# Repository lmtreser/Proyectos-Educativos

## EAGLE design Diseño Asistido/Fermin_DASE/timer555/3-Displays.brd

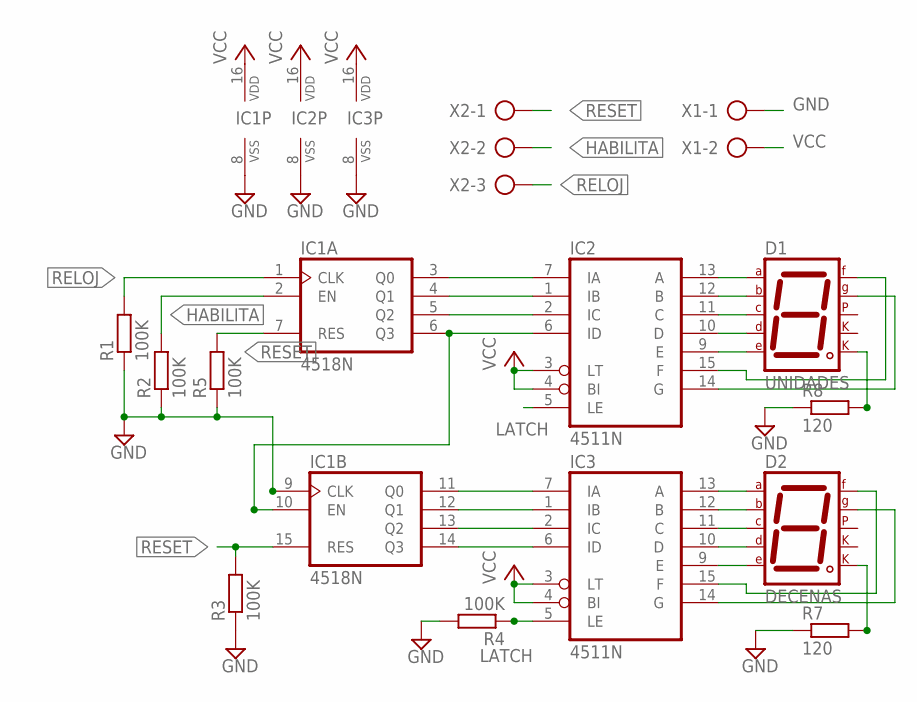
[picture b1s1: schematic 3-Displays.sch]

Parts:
D1: UNIDADES; 7SEG-13
D2: DECENAS; 7SEG-13
IC1: 4518N; DIL16
IC2, IC3: 4511N; DIL16
R1, R2, R3, R4, R5: 100K; 0207/7
R7, R8: 120; 0207/7
X1: AK500/2-H
X2: AK500/3-H

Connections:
GND: IC1.8 (VSS), IC1.9 (CLK), IC2.8 (VSS), IC3.8 (VSS), R1.1, R2.1, R3.1, R4.2, R5.1, R7.1, R8.1, X1.1
HABILITA: IC1.2 (EN), R2.2, X2.2
LATCH: IC2.5 (LE), IC3.5 (LE), R4.1
unnamed: IC1.3 (Q0), IC2.7 (IA)
unnamed: IC1.4 (Q1), IC2.1 (IB)
unnamed: IC1.5 (Q2), IC2.2 (IC)
unnamed: D1.8 (CK2), R8.2
unnamed: D2.7 (A), IC3.13 (A)
unnamed: D2.6 (B), IC3.12 (B)
unnamed: D2.4 (C), IC3.11 (C)
unnamed: D2.2 (D), IC3.10 (D)
unnamed: D2.1 (E), IC3.9 (E)
unnamed: IC1.11 (Q0), IC3.7 (IA)
unnamed: IC1.12 (Q1), IC3.1 (IB)
unnamed: IC1.14 (Q3), IC3.6 (ID)
unnamed: IC1.13 (Q2), IC3.2 (IC)
unnamed: D2.9 (F), IC3.15 (F)
unnamed: D2.10 (G), IC3.14 (G)
unnamed: D2.8 (CK2), R7.2
unnamed: D1.7 (A), IC2.13 (A)
unnamed: D1.6 (B), IC2.12 (B)
unnamed: D1.4 (C), IC2.11 (C)
unnamed: D1.2 (D), IC2.10 (D)
unnamed: D1.1 (E), IC2.9 (E)
unnamed: D1.9 (F), IC2.15 (F)
unnamed: D1.10 (G), IC2.14 (G)
unnamed: IC1.6 (Q3), IC1.10 (EN), IC2.6 (ID)
RELOJ: IC1.1 (CLK), R1.2, X2.3
RESET: IC1.7 (RES), IC1.15 (RES), R3.2, R5.2, X2.1
VCC: IC1.16 (VDD), IC2.3 (LT), IC2.4 (BI), IC2.16 (VDD), IC3.3 (LT), IC3.4 (BI), IC3.16 (VDD), X1.2

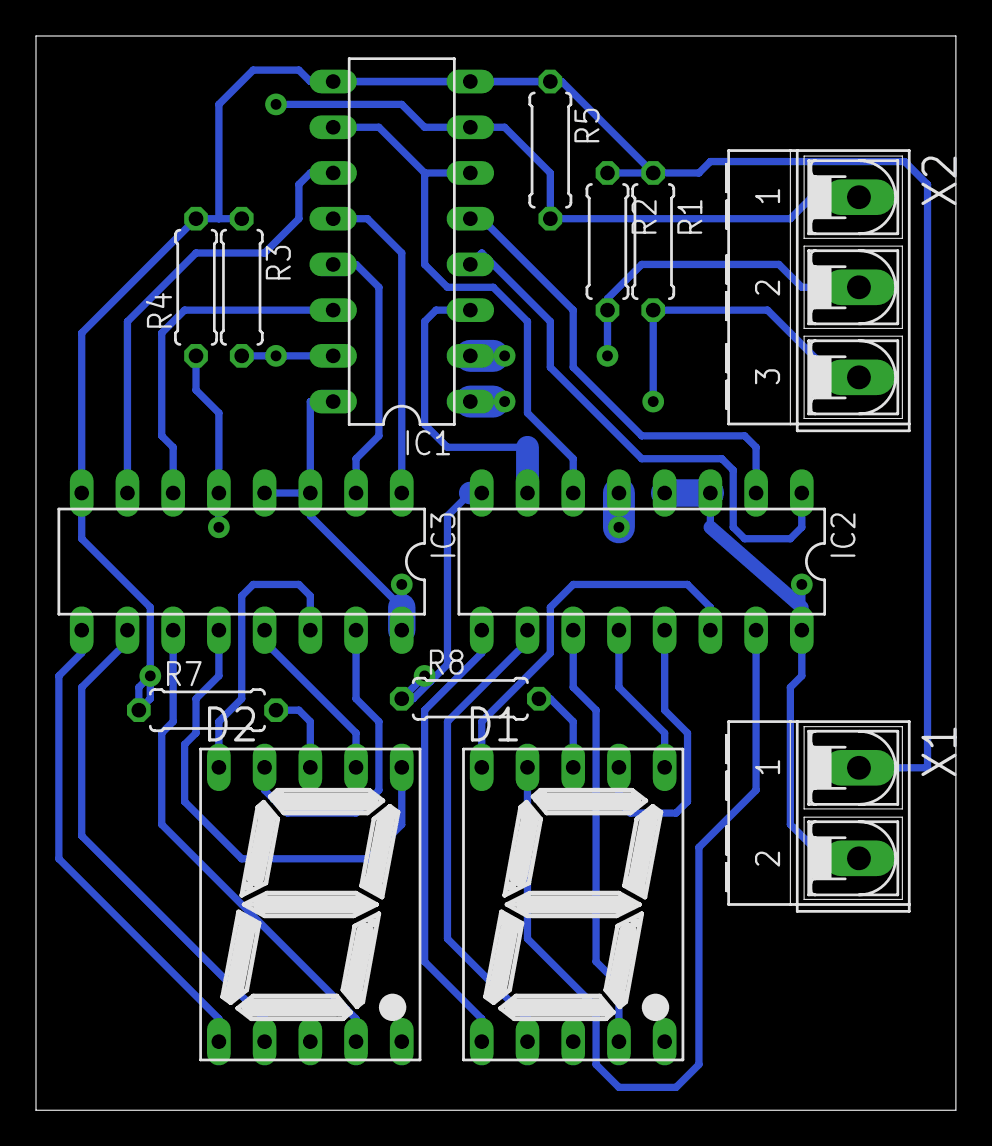
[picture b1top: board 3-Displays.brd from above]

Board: 2 copper layers, 51.1 x 59.7 mm, 14 parts (0 on the bottom side), 30 nets.

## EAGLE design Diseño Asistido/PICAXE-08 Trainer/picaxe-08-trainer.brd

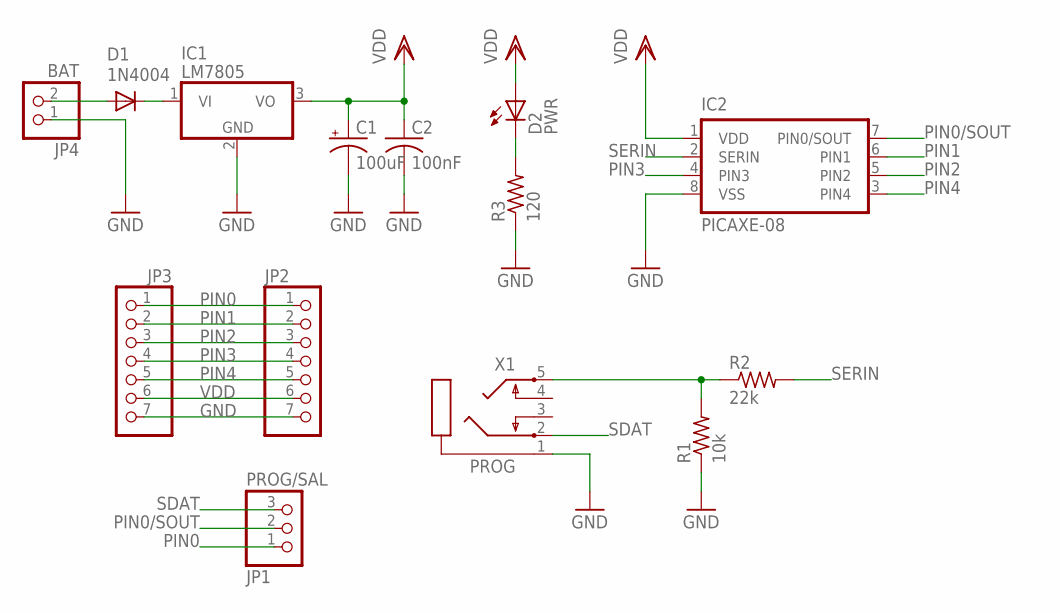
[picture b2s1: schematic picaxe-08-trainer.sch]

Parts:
C1: 100uF; E5-6
C2: 100nF; C025-025X050
D1: 1N4004; DO41-10
D2: PWR; LED3MM
IC1: LM7805; TO220V
IC2: PICAXE-08; DIL8
JP1: PROG/SAL; 1X03
JP2, JP3: PINHD-1X7; 1X07
JP4: BAT; 1X02
R1: 10k; 0204/7
R2: 22k; 0204/7
R3: 120; 0204/7
X1: PROG; STX3100

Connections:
GND: C1.-, C2.2, IC1.2 (GND), IC2.8 (VSS), JP2.7, JP3.7, JP4.1, R1.1, R3.1, X1.1
unnamed: D1.C, IC1.1 (VI)
unnamed: R1.2, R2.1, X1.5
unnamed: D2.K (C), R3.2
unnamed: D1.A, JP4.2
PIN0: JP1.1, JP2.1, JP3.1
PIN0/SOUT: IC2.7 (PIN0/SOUT), JP1.2
PIN1: IC2.6 (PIN1), JP2.2, JP3.2
PIN2: IC2.5 (PIN2), JP2.3, JP3.3
PIN3: IC2.4 (PIN3), JP2.4, JP3.4
PIN4: IC2.3 (PIN4), JP2.5, JP3.5
SDAT: JP1.3, X1.2
SERIN: IC2.2 (SERIN), R2.2
VDD: C1.+, C2.1, D2.A, IC1.3 (VO), IC2.1 (VDD), JP2.6, JP3.6

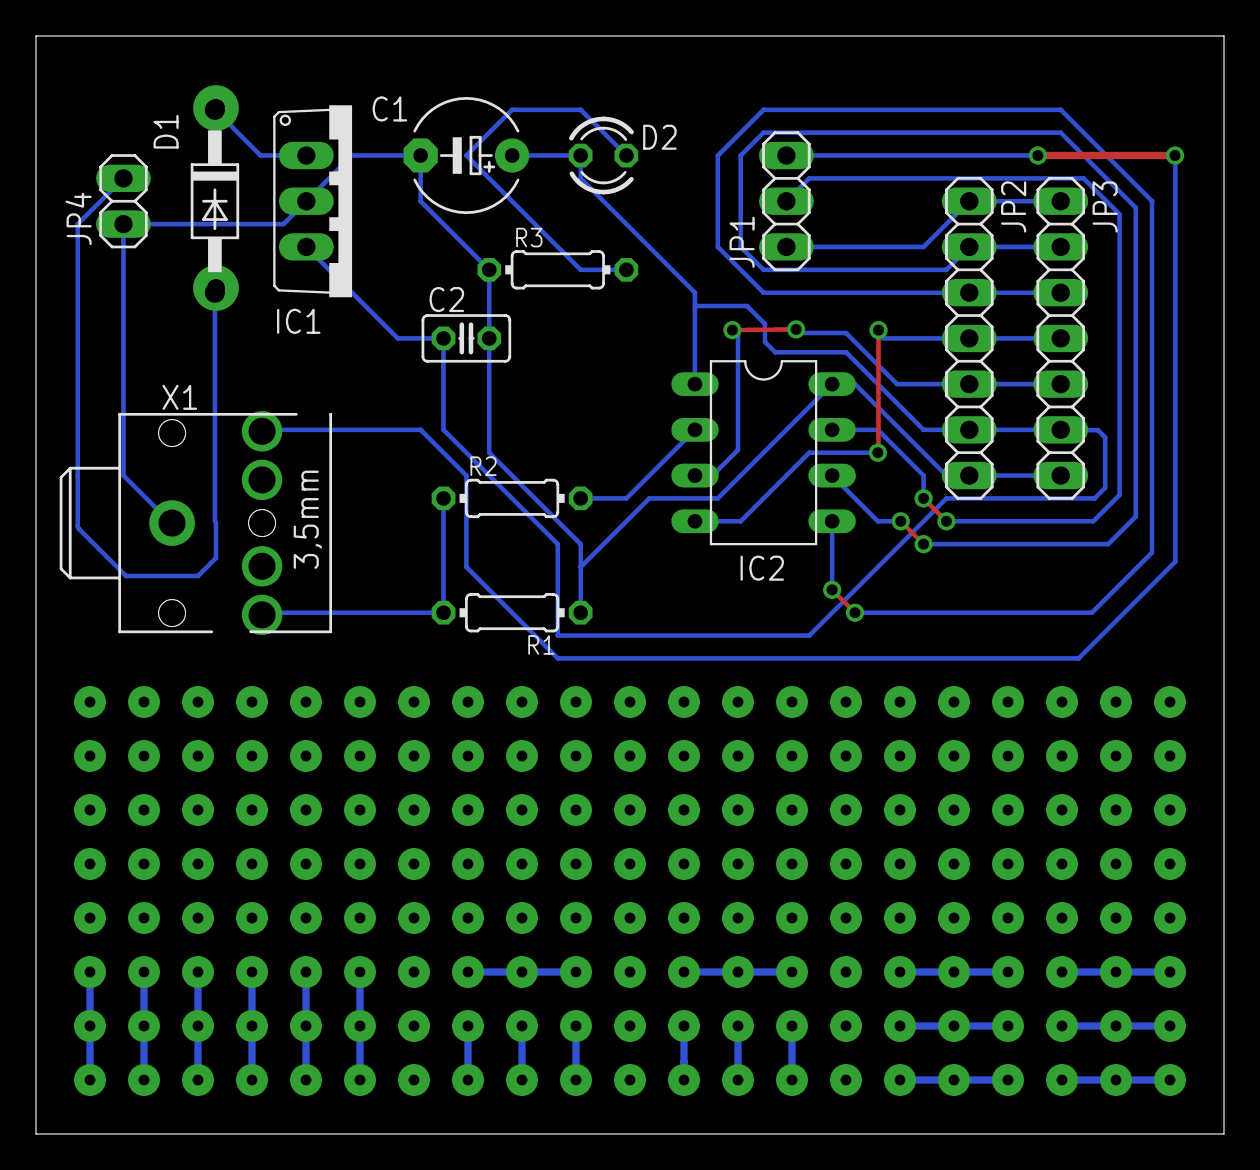
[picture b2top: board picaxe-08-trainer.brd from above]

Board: 2 copper layers, 66.0 x 61.0 mm, 14 parts (0 on the bottom side), 14 nets.

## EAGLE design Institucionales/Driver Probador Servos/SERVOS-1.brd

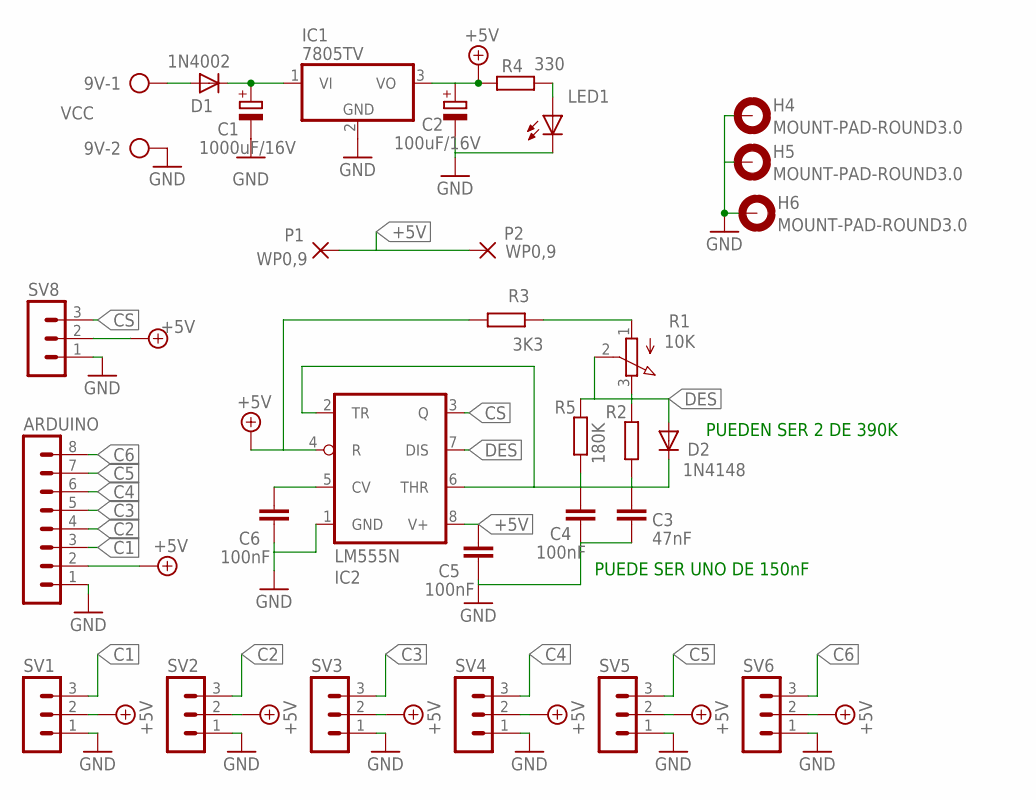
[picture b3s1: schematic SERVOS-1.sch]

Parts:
9V: VCC; AK500/2
ARDUINO: MA08-1
C1: 1000uF/16V; E2,5-7
C2: 100uF/16V; E2,5-5
C3: 47nF; C025_050-025X075
C4, C5, C6: 100nF; C025_050-025X075
D1: 1N4002; DO35-7
D2: 1N4148; DO35-7
H4, H5, H6: MOUNT-PAD-ROUND3.0; 3,0-PAD
IC1: 7805TV; TO220V
IC2: LM555N; DIL08
LED1: LED3MM
P1, P2: WP0,9; 1,6/0,9
R1: 10K; 3RP/1610N
R2: R-EU_0207/10; 0207/10
R3: 3K3; 0207/10
R4: 330; 0207/10
R5: 180K; 0207/10
SV1, SV2, SV3, SV4, SV5, SV6, SV8: MA03-1

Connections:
+5V: ARDUINO.2, C2.+, C5.1, IC1.3 (VO), IC2.4 (R), IC2.8 (V+), P1.1, P2.1, R3.2, R4.1, SV1.2, SV2.2, SV3.2, SV4.2, SV5.2, SV6.2, SV8.2
C1: ARDUINO.3, SV1.3
C2: ARDUINO.4, SV2.3
C3: ARDUINO.5, SV3.3
C4: ARDUINO.6, SV4.3
C5: ARDUINO.7, SV5.3
C6: ARDUINO.8, SV6.3
CS: IC2.3 (Q), SV8.3
DES: D2.A, IC2.7 (DIS), R1.2 (S), R1.3 (E), R2.2, R5.2
GND: 9V.2, ARDUINO.1, C1.-, C2.-, C3.2, C4.2, C5.2, C6.2, H4.B3,0, H5.B3,0, H6.B3,0, IC1.2 (GND), IC2.1 (GND), LED1.K (C), SV1.1, SV2.1, SV3.1, SV4.1, SV5.1, SV6.1, SV8.1
unnamed: C1.+, D1.C, IC1.1 (VI)
unnamed: 9V.1, D1.A
unnamed: LED1.A, R4.2
unnamed: C6.1, IC2.5 (CV)
unnamed: R1.1 (A), R3.1
unnamed: C3.1, C4.1, D2.C, IC2.2 (TR), IC2.6 (THR), R2.1, R5.1

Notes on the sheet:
PUEDE SER UNO DE 150nF
PUEDEN SER 2 DE 390K

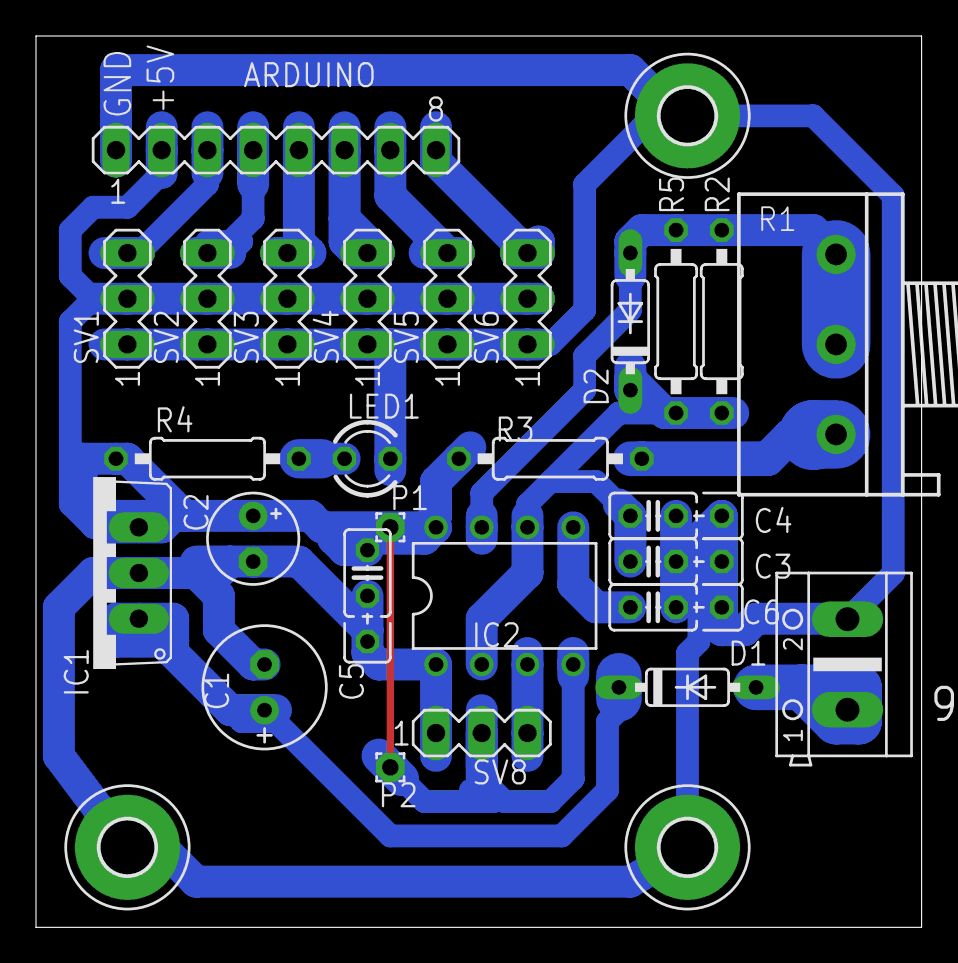
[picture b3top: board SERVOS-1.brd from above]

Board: 2 copper layers, 49.2 x 49.5 mm, 30 parts (0 on the bottom side), 16 nets.

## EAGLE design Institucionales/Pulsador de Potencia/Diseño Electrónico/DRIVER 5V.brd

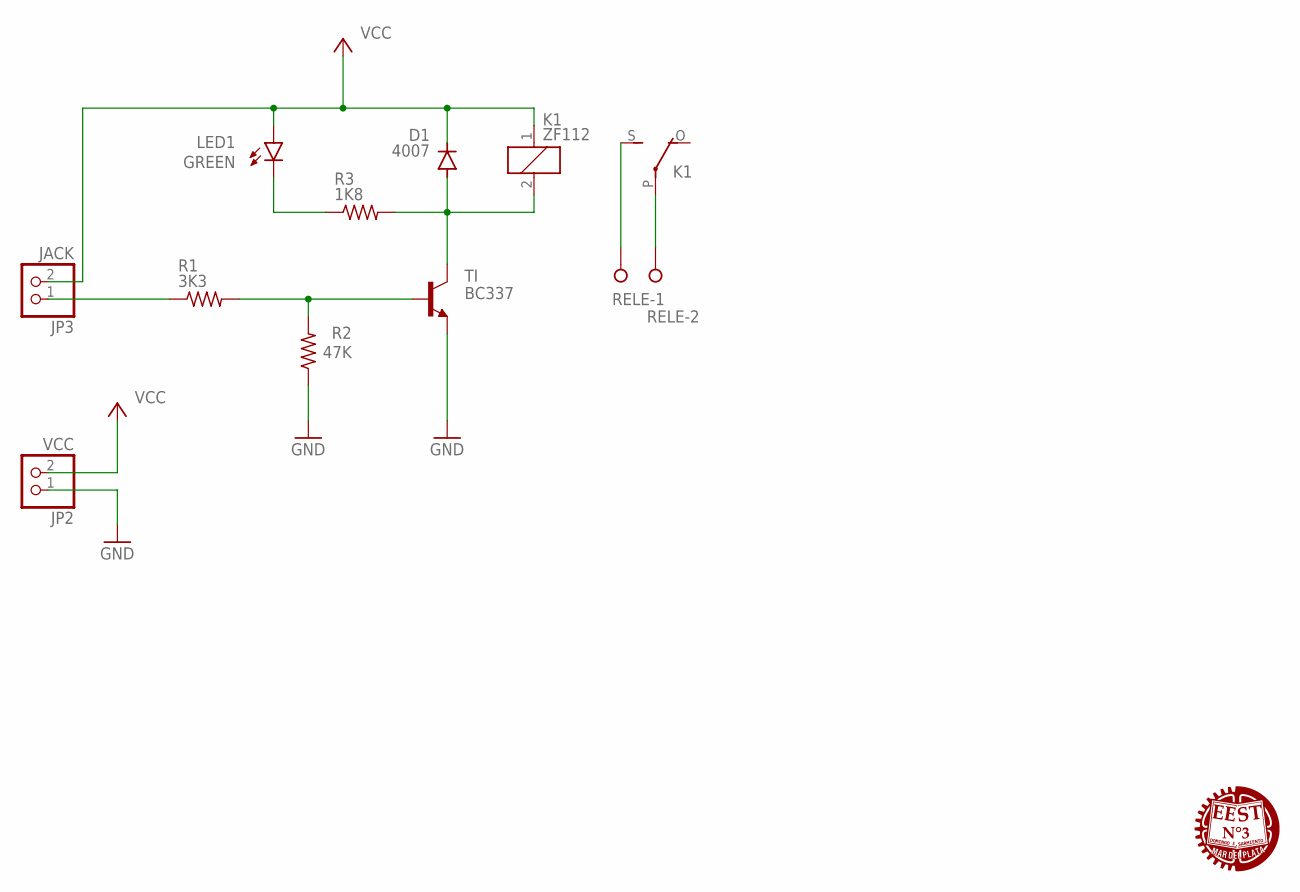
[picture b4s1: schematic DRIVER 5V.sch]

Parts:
D1: 4007; DO35-10
JP2: VCC; 1X02
JP3: JACK; 1X02
K1: ZF112
LED1: GREEN; LED5MM
R1: 3K3; 0207/10
R2: 47K; 0207/10
R3: 1K8; 0207/10
RELE: W237-02P; W237-132
TI: BC337; TO92-CBE
U$1: LOGO_EEST_N3; LOGO_EEST_N3_250

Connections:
GND: JP2.1, R2.1, TI.E
unnamed: JP3.1, R1.1
unnamed: R1.2, R2.2, TI.B
unnamed: D1.A, K1.2, R3.2, TI.C
unnamed: LED1.K (C), R3.1
unnamed: K1.S, RELE.1
unnamed: K1.P, RELE.2
VCC: D1.C, JP2.2, JP3.2, K1.1, LED1.A

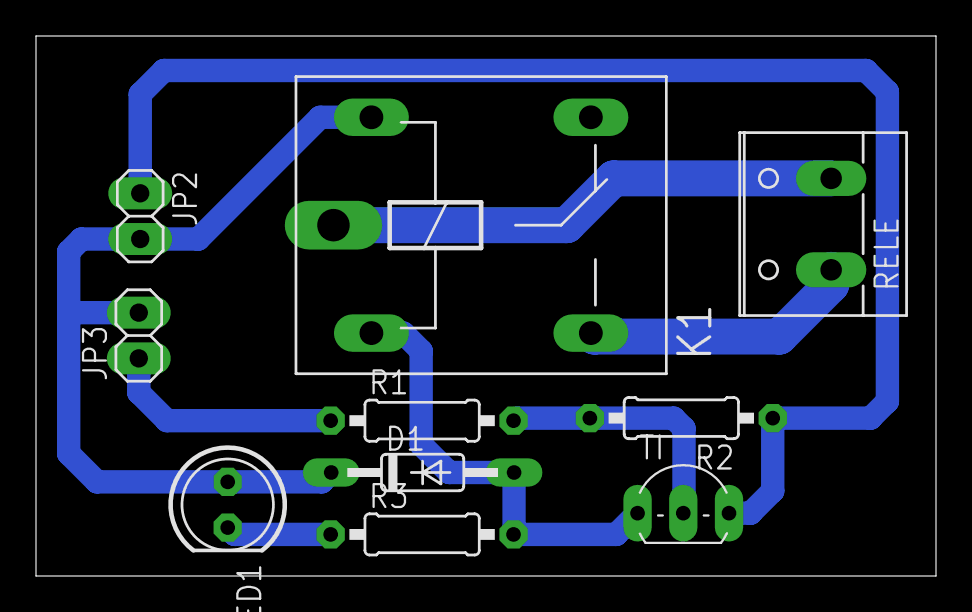
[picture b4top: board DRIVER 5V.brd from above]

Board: 2 copper layers, 50.0 x 30.0 mm, 11 parts (0 on the bottom side), 8 nets.

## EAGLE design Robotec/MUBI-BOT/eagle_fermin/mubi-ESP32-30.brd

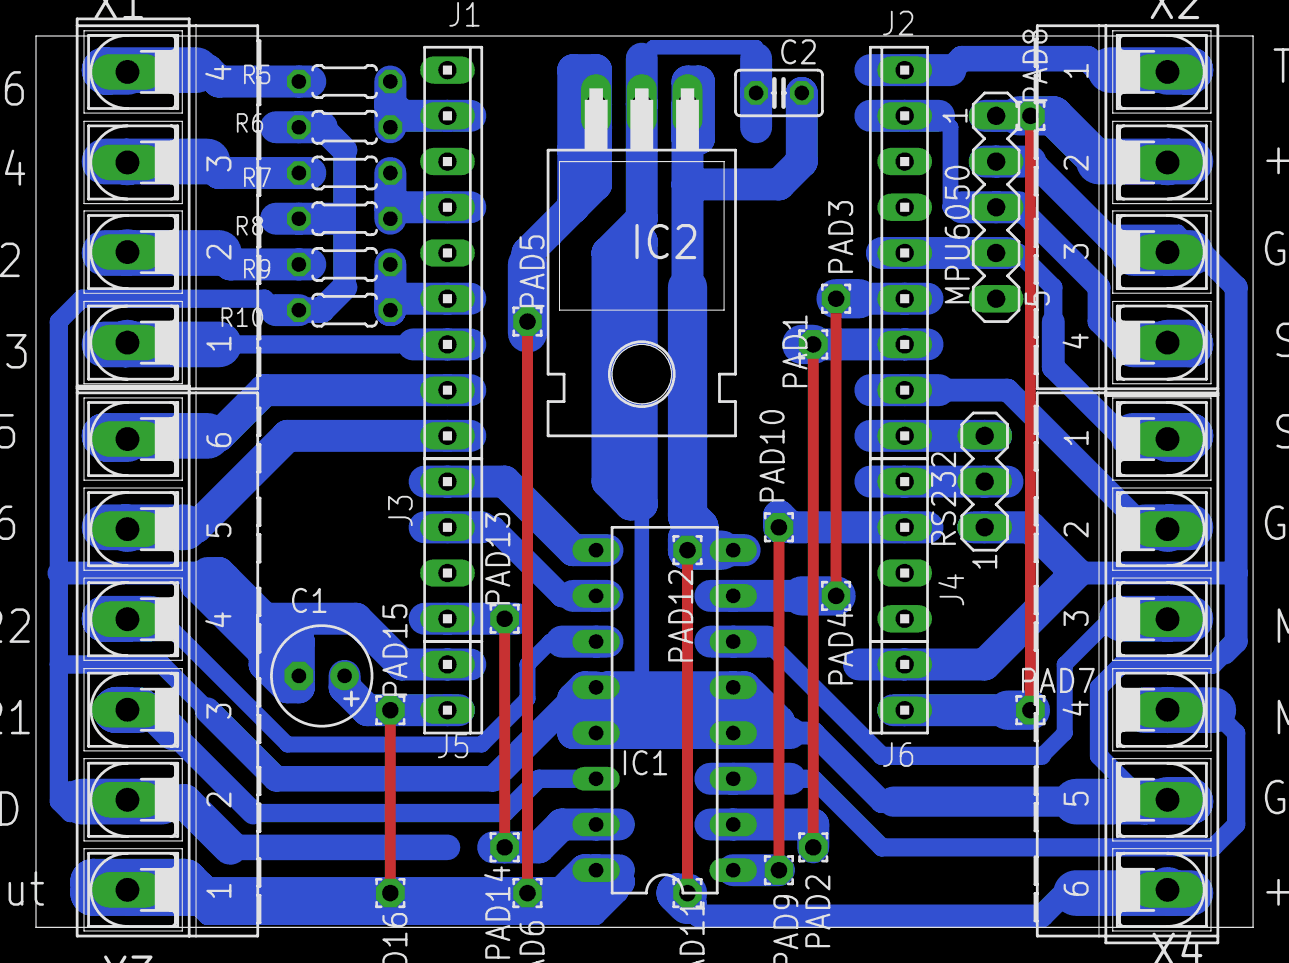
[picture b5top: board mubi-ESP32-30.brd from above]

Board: 2 copper layers, 67.6 x 49.5 mm, 38 parts (0 on the bottom side), 29 nets.

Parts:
C1: E2,5-6
C2: C025-025X050
IC1: L293D; DIL16
IC2: 7805T; TO220H
J1, J2: 10X09MTA
J3, J4: 10X04MTA
J5, J6: 10X02MTA
MPU6050: MA05-1
PAD1, PAD2, PAD3, PAD4, PAD5, PAD6, PAD7, PAD8, PAD9, PAD10, PAD11, PAD12, PAD13, PAD14, PAD15, PAD16: WIREPAD1,6/0,9; 1,6/0,9
R5, R7, R9: 5K6; 0204/5
R6, R8, R10: 10K; 0204/5
RS232: MA03-1
X1, X2: AK500/4-H
X3, X4: AK500/6-H

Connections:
+3.3V: J6.2, MPU6050.1, PAD7.1, PAD8.1, X2.2
+5V: C1.+, IC1.16, IC2.3, J5.1, PAD5.1, PAD6.1, PAD15.1, PAD16.1, X3.1
+VBAT: C2.1, IC1.8, IC2.1, PAD11.1, PAD12.1, X4.6
CM11: IC1.2, J2.7, PAD1.1, PAD2.1
CM12: IC1.7, J2.6, PAD3.1, PAD4.1
CM21: IC1.15, J3.1, PAD13.1, PAD14.1
CM22: IC1.10, J3.3
ENAM1: IC1.1, J4.2, PAD9.1, PAD10.1
ENAM2: IC1.9, J3.4
GND: C1.-, C2.2, IC1.4, IC1.5, IC1.12, IC1.13, IC2.2, J5.2, J6.1, MPU6050.2, R6.2, R8.2, R10.2, RS232.1, X2.3, X3.2, X4.5
GPI34: J1.6, R7.2, R8.1
GPI36: J1.8, R5.2, R6.1
GPIO5: J2.8, X4.2
GPIO23: J2.1, X2.1
GPIO25: J1.2, X3.6
GPIO26: J1.1, X3.5
GPIO32: J1.4, R9.2, R10.1
GPIO33: J1.3, X1.1
M11: IC1.3, X4.4
M12: IC1.6, X4.3
M21: IC1.14, X3.3
M22: IC1.11, X3.4
unnamed: R5.1, X1.4
unnamed: R7.1, X1.3
unnamed: R9.1, X1.2
RX2: J4.1, RS232.2
SCL: J2.2, MPU6050.3, X2.4
SDA: J2.5, MPU6050.4, X4.1
TX2: J2.9, RS232.3

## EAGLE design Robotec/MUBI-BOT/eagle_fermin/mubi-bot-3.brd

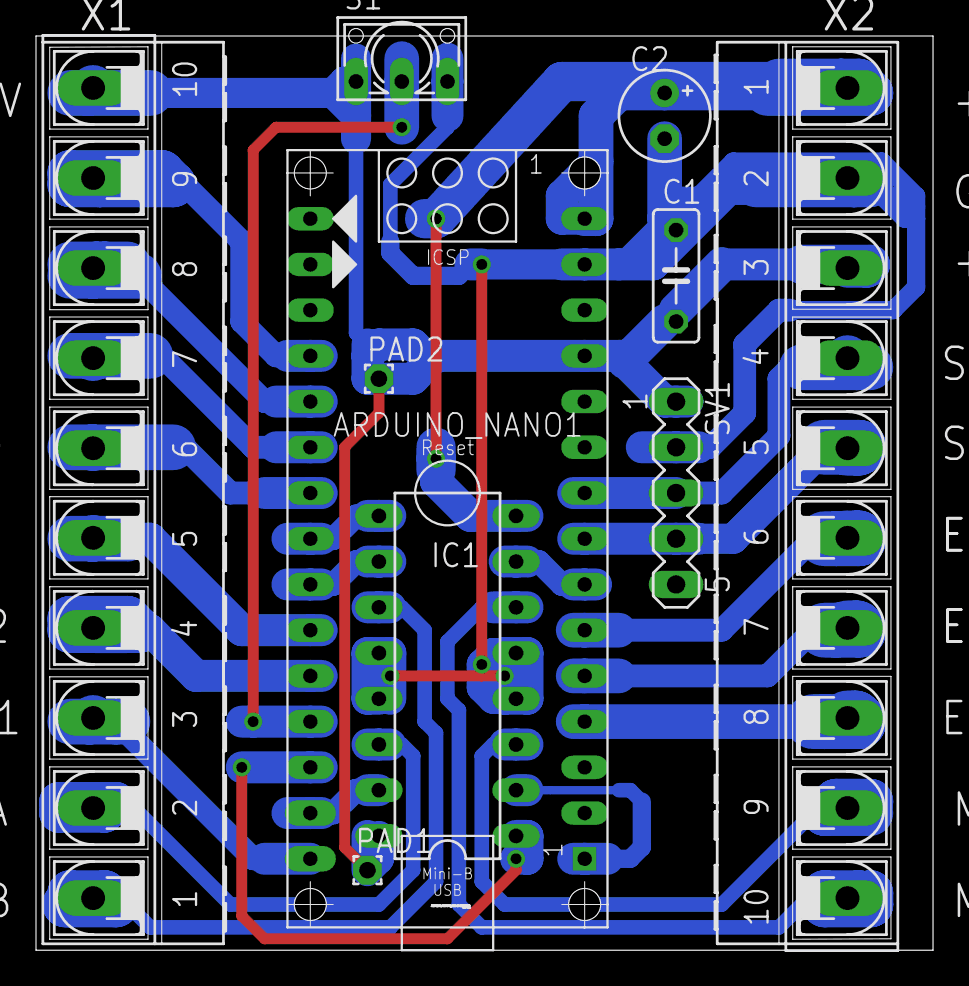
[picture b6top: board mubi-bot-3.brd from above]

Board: 2 copper layers, 49.8 x 50.8 mm, 10 parts (0 on the bottom side), 26 nets.

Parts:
ARDUINO_NANO1: ARDUINO_NANO
C1: C050-025X075
C2: E2,5-5
IC1: L293E; DIL16
PAD1, PAD2: WIREPAD1,6/0,9; 1,6/0,9
S1: 9450-1
SV1: MA05-1
X1, X2: AK500/10-H

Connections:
+5V: ARDUINO_NANO1.12, C1.1, IC1.16, PAD1.1, PAD2.1, S1.1, SV1.1, X1.10, X2.3
+VBAT: ARDUINO_NANO1.15, C2.+, IC1.8, X2.1
AUX1: ARDUINO_NANO1.30, X1.3
AUX2: ARDUINO_NANO1.26, X1.4
CM11: ARDUINO_NANO1.1, IC1.2
CM12: ARDUINO_NANO1.7, IC1.7
CM21: ARDUINO_NANO1.29, IC1.15
CM22: ARDUINO_NANO1.24, IC1.10
ECHO1: ARDUINO_NANO1.4, X2.8
ECHO2: ARDUINO_NANO1.5, X2.7
ECHO3: ARDUINO_NANO1.6, X2.6
ENA1: ARDUINO_NANO1.28, IC1.1
ENA2: ARDUINO_NANO1.23, IC1.9
GND: ARDUINO_NANO1.14, ARDUINO_NANO1.19, C1.2, C2.-, IC1.12, IC1.13, S1.3, SV1.2, X1.9, X2.2
INFRA1: ARDUINO_NANO1.21, X1.7
INFRA2: ARDUINO_NANO1.22, X1.6
INFRA3: ARDUINO_NANO1.25, X1.5
M1A: IC1.3, X2.9
M1B: IC1.6, X2.10
M2A: IC1.14, X1.2
M2B: IC1.11, X1.1
unnamed: IC1.4, IC1.5
unnamed: ARDUINO_NANO1.27, S1.2
SCL: ARDUINO_NANO1.9, SV1.3, X2.4
SDA: ARDUINO_NANO1.8, SV1.4, X2.5
TRIG: ARDUINO_NANO1.20, X1.8
